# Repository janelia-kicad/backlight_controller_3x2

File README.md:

- [Repository Information](#org4660580)
  - [Description](#org6dcabe7)
- [Images](#org285c25f)
- [Schematic](#orgf1630ab)
- [Gerbers](#org91c6de4)
- [Bill of Materials](#orgdd32f43)
  - [PCB Parts](#org0175e16)
  - [Supplemental Parts](#orgda2eed9)
  - [Vendor Parts Lists](#orgb926b52)
- [Supplemental Documentation](#org7f741fd)
  - [Assembly Instructions](#orgb29884f)

# Repository Information

-   **Name:** backlight\_controller\_3x2
-   **Version:** 1.2
-   **License:** Open-Source Hardware
-   **URL:** <https://github.com/janelia-kicad/backlight_controller_3x2>
-   **Author:** Peter Polidoro
-   **Email:** peter@polidoro.io

## Description

This board controls one Smart Vision backlight with IR and visible channels plus additional high and low power channel outputs.

# Images

# Schematic

[./schematic/backlight\_controller\_3x2.pdf](./schematic/backlight_controller_3x2.pdf)

# Gerbers

Send gerbers zip file to your favorite PCB manufacturer for fabrication.

[./gerbers/backlight\_controller\_3x2\_v1.2.zip](./gerbers/backlight_controller_3x2_v1.2.zip)

# Bill of Materials

## PCB Parts

| Item | Reference(s)                    | Quantity | PartNumber         | Vendor  | Description                                                               |
|---- |------------------------------- |-------- |------------------ |------- |------------------------------------------------------------------------- |
| 1    | C1 C2 C3 C4 C5 C6               | 6        | 399-13229-1-ND     | digikey | CAP CER 0.1UF 50V 10% X7R 1210                                            |
| 2    | D1                              | 1        | 568-11697-1-ND     | digikey | DIODE SCHOTTKY 45V 10A CFP15                                              |
| 3    | HPS1 HPS2 HPS3 HPS4             | 4        | BTS3256DAUMA1CT-ND | digikey | IC SWITCH SMART LOWSIDE TO252-5                                           |
| 4    | J1                              | 1        | 1195-4005-1-ND     | digikey | CONN D-SUB RCPT 9POS SMD SOLDER                                           |
| 5    | J2                              | 1        | 1195-4006-1-ND     | digikey | CONN D-SUB PLUG 9POS SMD SOLDER                                           |
| 6    | J3 J4                           | 2        | 277-10282-1-ND     | digikey | CONN FMALE INSERT 5POS SOLDER                                             |
| 7    | L1                              | 1        | 350-1723-ND        | digikey | LED 2MM 24V VERTICAL RED PC MNT                                           |
| 8    | L10 L11 L2 L3 L4 L5 L6 L7 L8 L9 | 10       | 350-1726-ND        | digikey | LED 2MM 5V VERTICAL GREEN PC MNT                                          |
| 9    | MDB1                            | 2        | S1011E-16-ND       | digikey | 16 Position Header Through Hole Male Pins                                 |
| 10   | P1                              | 1        | WM1353-ND          | digikey | CONN HEADER 6POS 4.2MM R/A TIN                                            |
| 11   | R1 R2 R3 R4                     | 4        | P5.90KAACT-ND      | digikey | RES SMD 5.9k OHM 1% 1/2W 1210                                             |
| 12   | R5 R6 R7 R8                     | 4        | P75.0CCT-ND        | digikey | RES SMD 75 OHM 1% 1/8W 0805                                               |
| 13   | U1 U2                           | 2        | 296-14668-1-ND     | digikey | Buffer Non-Inverting 1 Element 8 Bit per Element Push-Pull Output 20-SOIC |
| 14   | U3 U4                           | 2        | NUD3124LT1GOSCT-ND | digikey | IC INDCT LOAD DRVR AUTO SOT23                                             |

## Supplemental Parts

| Item | Quantity | PartNumber   | Vendor  | Description                    |
|---- |-------- |------------ |------- |------------------------------ |
| 1    | 1        | 1866-2122-ND | digikey | AC/DC DESKTOP ADAPTER 24V 280W |
| 2    | 1        | 1866-5006-ND | digikey | CORD IEC 320-C13 6FT BLACK     |
| 3    | 2        | 277-10308-ND | digikey | CONN INSERT SHELL PRESS FIT    |

## Vendor Parts Lists

[./bom/digikey\_parts.csv](./bom/digikey_parts.csv)

[./bom/supplemental\_digikey\_parts.csv](./bom/supplemental_digikey_parts.csv)

# Supplemental Documentation

## Assembly Instructions

-   Solder surface mount and through hole components onto the pcb.

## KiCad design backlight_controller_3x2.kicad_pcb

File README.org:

# Created 2018-10-29 Mon 13:45
#+OPTIONS: title:nil author:nil email:nil toc:t |:t ^:nil
* Repository Information

- Name :: backlight_controller_3x2
- Version :: 1.2
- License :: Open-Source Hardware
- URL :: https://github.com/janelia-kicad/backlight_controller_3x2
- Author :: Peter Polidoro
- Email :: peter@polidoro.io

** Description

This board controls one Smart Vision backlight with IR and visible channels
plus additional high and low power channel outputs.

* Images

* Schematic

[[file:./schematic/backlight_controller_3x2.pdf][./schematic/backlight_controller_3x2.pdf]]

[[file:./schematic/images/schematic00.png]]

[[file:./schematic/images/schematic01.png]]

[[file:./schematic/images/schematic02.png]]

[[file:./schematic/images/schematic03.png]]

[[file:./schematic/images/schematic04.png]]

[[file:./schematic/images/schematic05.png]]

[[file:./schematic/images/schematic06.png]]

[[file:./schematic/images/schematic07.png]]

[[file:./schematic/images/schematic08.png]]

[[file:./schematic/images/schematic09.png]]

[[file:./schematic/images/schematic10.png]]

[[file:./schematic/images/schematic11.png]]

[[file:./schematic/images/schematic12.png]]

[[file:./schematic/images/schematic13.png]]

[[file:./schematic/images/schematic14.png]]

* Gerbers

Send gerbers zip file to your favorite PCB manufacturer for fabrication.

[[file:./gerbers/backlight_controller_3x2_v1.2.zip][./gerbers/backlight_controller_3x2_v1.2.zip]]

[[file:./gerbers/images/gerbers00.png]]

[[file:./gerbers/images/gerbers01.png]]

* Bill of Materials

** PCB Parts

| Item | Reference(s)                    | Quantity | PartNumber         | Vendor  | Description                                                               |
|------+---------------------------------+----------+--------------------+---------+---------------------------------------------------------------------------|
|    1 | C1 C2 C3 C4 C5 C6               |        6 | 399-13229-1-ND     | digikey | CAP CER 0.1UF 50V 10% X7R 1210                                            |
|    2 | D1                              |        1 | 568-11697-1-ND     | digikey | DIODE SCHOTTKY 45V 10A CFP15                                              |
|    3 | HPS1 HPS2 HPS3 HPS4             |        4 | BTS3256DAUMA1CT-ND | digikey | IC SWITCH SMART LOWSIDE TO252-5                                           |
|    4 | J1                              |        1 | 1195-4005-1-ND     | digikey | CONN D-SUB RCPT 9POS SMD SOLDER                                           |
|    5 | J2                              |        1 | 1195-4006-1-ND     | digikey | CONN D-SUB PLUG 9POS SMD SOLDER                                           |
|    6 | J3 J4                           |        2 | 277-10282-1-ND     | digikey | CONN FMALE INSERT 5POS SOLDER                                             |
|    7 | L1                              |        1 | 350-1723-ND        | digikey | LED 2MM 24V VERTICAL RED PC MNT                                           |
|    8 | L10 L11 L2 L3 L4 L5 L6 L7 L8 L9 |       10 | 350-1726-ND        | digikey | LED 2MM 5V VERTICAL GREEN PC MNT                                          |
|    9 | MDB1                            |        2 | S1011E-16-ND       | digikey | 16 Position Header Through Hole Male Pins                                 |
|   10 | P1                              |        1 | WM1353-ND          | digikey | CONN HEADER 6POS 4.2MM R/A TIN                                            |
|   11 | R1 R2 R3 R4                     |        4 | P5.90KAACT-ND      | digikey | RES SMD 5.9k OHM 1% 1/2W 1210                                             |
|   12 | R5 R6 R7 R8                     |        4 | P75.0CCT-ND        | digikey | RES SMD 75 OHM 1% 1/8W 0805                                               |
|   13 | U1 U2                           |        2 | 296-14668-1-ND     | digikey | Buffer Non-Inverting 1 Element 8 Bit per Element Push-Pull Output 20-SOIC |
|   14 | U3 U4                           |        2 | NUD3124LT1GOSCT-ND | digikey | IC INDCT LOAD DRVR AUTO SOT23                                             |

** Supplemental Parts

| Item | Quantity | PartNumber   | Vendor  | Description                    |
|------+----------+--------------+---------+--------------------------------|
|    1 |        1 | 1866-2122-ND | digikey | AC/DC DESKTOP ADAPTER 24V 280W |
|    2 |        1 | 1866-5006-ND | digikey | CORD IEC 320-C13 6FT BLACK     |
|    3 |        2 | 277-10308-ND | digikey | CONN INSERT SHELL PRESS FIT    |

** Vendor Parts Lists

[[file:./bom/digikey_parts.csv][./bom/digikey_parts.csv]]

[[file:./bom/supplemental_digikey_parts.csv][./bom/supplemental_digikey_parts.csv]]

* Supplemental Documentation

** Assembly Instructions

- Solder surface mount and through hole components onto the pcb.

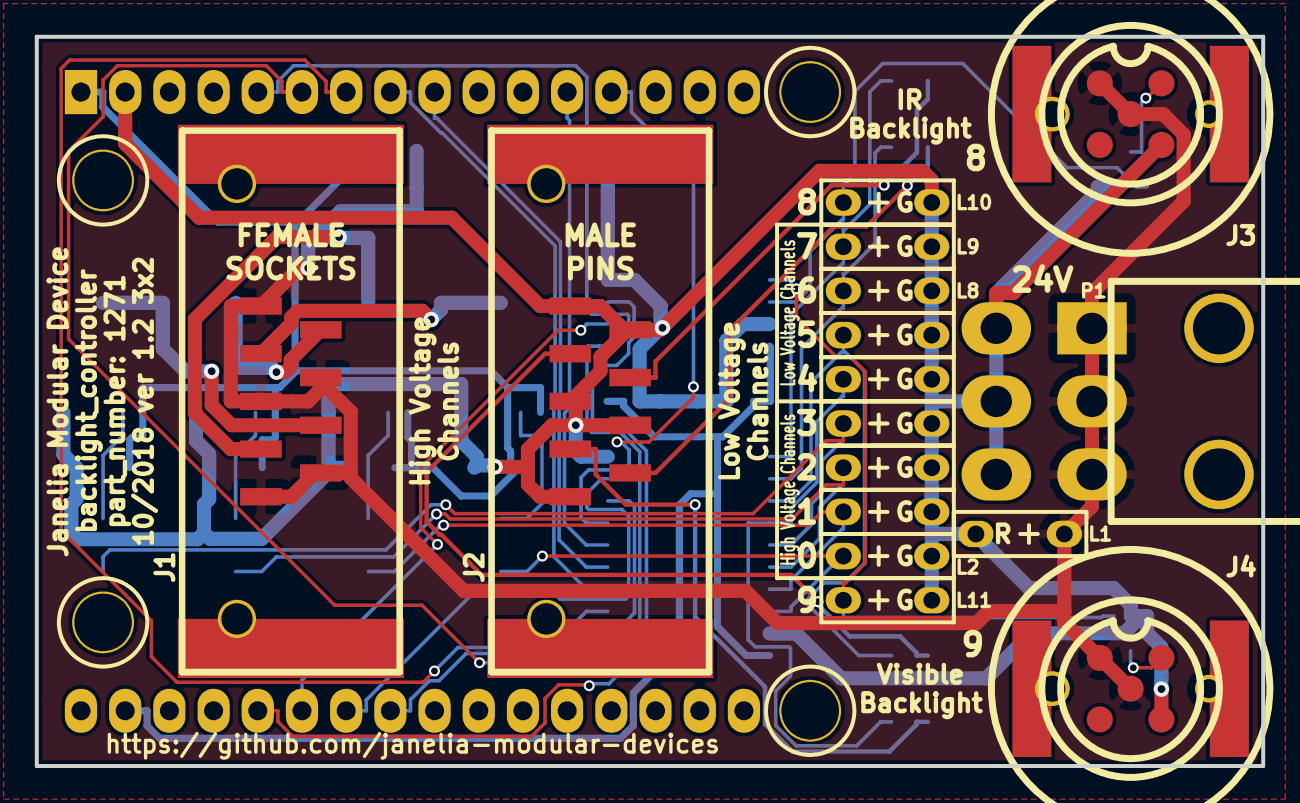
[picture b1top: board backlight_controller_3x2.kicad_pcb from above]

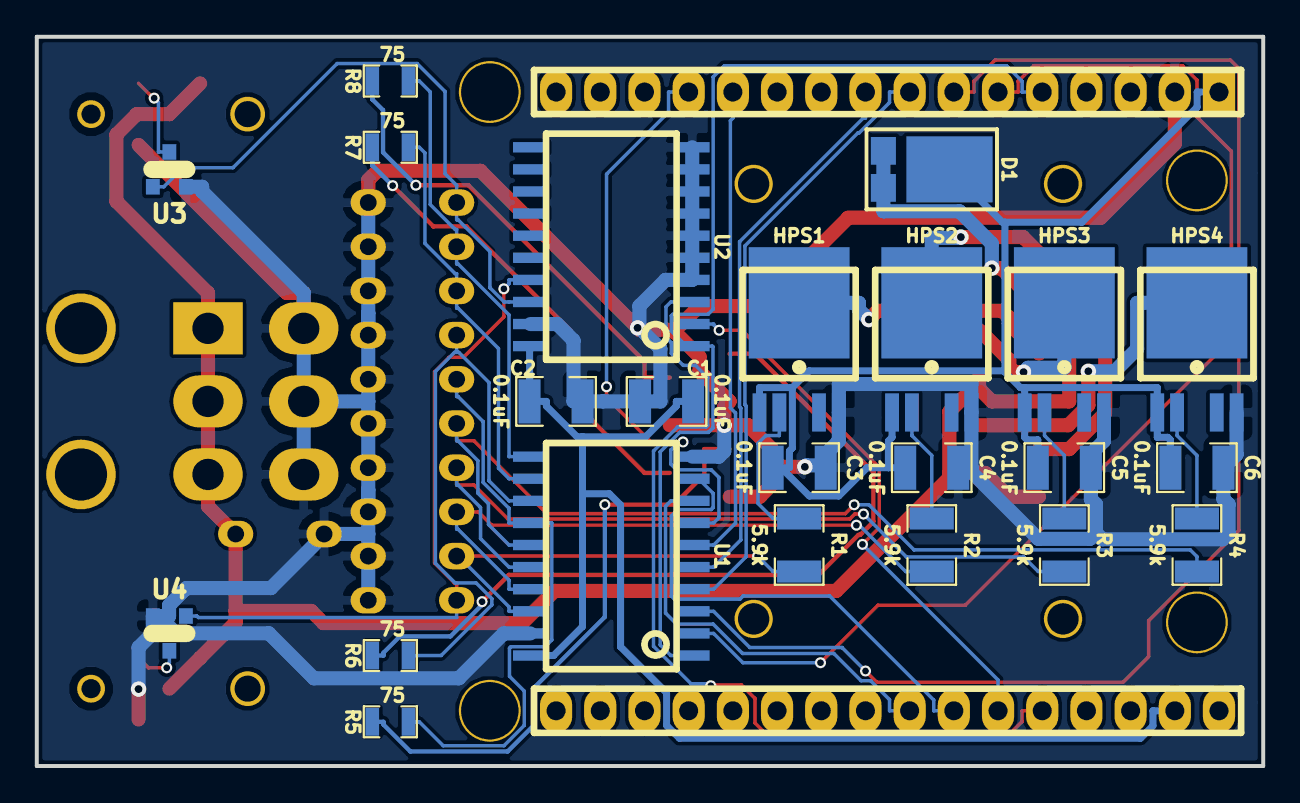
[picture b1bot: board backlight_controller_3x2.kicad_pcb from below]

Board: 2 copper layers, 70.5 x 41.9 mm, 40 parts (23 on the bottom side), 39 nets.

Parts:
C1, C2, C3, C4, C5, C6: 0.1uF; SM1210
D1: diode_schottky_45V_10A; CFP15
HPS1, HPS2, HPS3, HPS4: BTS3256; PG-TO252-5-11
J1: DB9F_SMD
J2: DB9M_SMD
J3, J4: M12-5-RCPT_F_SMD; M12-5_RCPT_F_SMD
L1: LED_24V_RED; LED_555-3XXX_R
L2, L3, L4, L5, L6, L7, L8, L9, L10, L11: LED_5V_GRN; LED_555-3XXX_G
MDB1: MODULAR_DEVICE_BASE_3X2_MALE
P1: MINI_FIT_JR_02X03_M_RA; MINI-FIT-JR_02X03_M_RA
R1, R2, R3, R4: 5.9k; SM1210
R5, R6, R7, R8: 75; SM0805
U1, U2: SN74ABT541BDWR; SOIC_20
U3, U4: NUD3124; TO-236-3

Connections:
/CHANNEL_0: MDB1.3, U1.2
/CHANNEL_1: MDB1.4, U1.3
/CHANNEL_2: MDB1.5, U1.4
/CHANNEL_3: MDB1.6, U1.5
/CHANNEL_4: MDB1.9, U1.6
/CHANNEL_5: MDB1.10, U1.7
/CHANNEL_6: MDB1.20, U1.8
/CHANNEL_7: MDB1.21, U1.9
/CHANNEL_8: MDB1.22, U2.2
/CHANNEL_9: MDB1.23, U2.3
/backlight_3x2/C_0: L2.1, R1.2, U1.18
/backlight_3x2/C_1: L3.1, R2.2, U1.17
/backlight_3x2/C_2: L4.1, R3.2, U1.16
/backlight_3x2/C_3: L5.1, R4.2, U1.15
/backlight_3x2/C_4: L6.1, R5.2, U1.14
/backlight_3x2/C_5: L7.1, R6.2, U1.13
/backlight_3x2/C_6: L8.1, R7.2, U1.12
/backlight_3x2/C_7: L9.1, R8.2, U1.11
/backlight_3x2/C_8: L10.1, U2.18, U3.1
/backlight_3x2/C_9: L11.1, U2.17, U4.1
/backlight_3x2/backlight_outputs/ir/NPN: J3.2, U3.3
/backlight_3x2/backlight_outputs/visible/NPN: J4.2, U4.3
/backlight_3x2/high_voltage_outputs/OUTPUT_0: HPS1.6, J1.2
/backlight_3x2/high_voltage_outputs/OUTPUT_1: HPS2.6, J1.4
/backlight_3x2/high_voltage_outputs/OUTPUT_2: HPS3.6, J1.6
/backlight_3x2/high_voltage_outputs/OUTPUT_3: HPS4.6, J1.8
/backlight_3x2/high_voltage_outputs/high_voltage_output_0/FAULT: HPS1.2, R1.1
/backlight_3x2/high_voltage_outputs/high_voltage_output_1/FAULT: HPS2.2, R2.1
/backlight_3x2/high_voltage_outputs/high_voltage_output_2/FAULT: HPS3.2, R3.1
/backlight_3x2/high_voltage_outputs/high_voltage_output_3/FAULT: HPS4.2, R4.1
/backlight_3x2/low_voltage_outputs/OUTPUT_0: J2.2, R5.1
/backlight_3x2/low_voltage_outputs/OUTPUT_1: J2.4, R6.1
/backlight_3x2/low_voltage_outputs/OUTPUT_2: J2.6, R7.1
/backlight_3x2/low_voltage_outputs/OUTPUT_3: J2.8, R8.1
/~ENABLE: MDB1.2, U1.1, U2.1
GND: C1.2, C2.2, C3.2, C4.2, C5.2, C6.2, HPS1.5, HPS2.5, HPS3.5, HPS4.5, J2.1, J2.3, J2.5, J2.7, J2.9, J3.3, J4.3, L1.2, L2.2, L3.2, L4.2, L5.2, L6.2, L7.2, L8.2, L9.2, L10.2, L11.2, MDB1.GND, P1.4, P1.5, P1.6, U1.10, U1.19, U2.4, U2.5, U2.6, U2.7, U2.8, U2.9, U2.10, U2.19, U3.2, U4.2
VAA: D1.2, J1.1, J1.3, J1.5, J1.7, J1.9, J3.1, J3.5, J4.1, J4.5, L1.1, P1.1, P1.2, P1.3
VDD: C3.1, C4.1, C5.1, C6.1, D1.1, HPS1.1, HPS2.1, HPS3.1, HPS4.1, MDB1.VDD
VEE: C1.1, C2.1, MDB1.VEE, U1.20, U2.20

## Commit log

2018-09-13 Initial commit.
2018-09-13 Added components and footprints.
2018-09-13 Added schematics.
2018-09-13 Initial layout.
2018-09-13 Finished version 1.0.
2018-09-14 Moved some pcb text.
2018-09-14 Added generate_kicad_documentation submodule.
2018-09-14 Updated documentation.
2018-10-19 Changes towards v1.1.
2018-10-19 More changes towards v1.1.
2018-10-20 Finished version 1.1.
2018-10-23 Updated documentation for version 1.1.
2018-10-23 Updated submodules.
2018-10-26 Updated supplemental bom.
2018-10-29 high_power -> high_voltage. low_power -> low_voltage.
2018-10-29 Progress towards v1.2.
2018-10-29 Finished v1.2 schematic.
2018-10-29 Finished v1.2.
2018-11-02 Added README.md.
2021-09-16 Update email address
2021-09-21 Remove ignored files
2022-02-22 Add guix files
2022-02-23 Add guix documentation
2022-06-29 Remove redundant guix files
2022-06-29 power -> user_power
